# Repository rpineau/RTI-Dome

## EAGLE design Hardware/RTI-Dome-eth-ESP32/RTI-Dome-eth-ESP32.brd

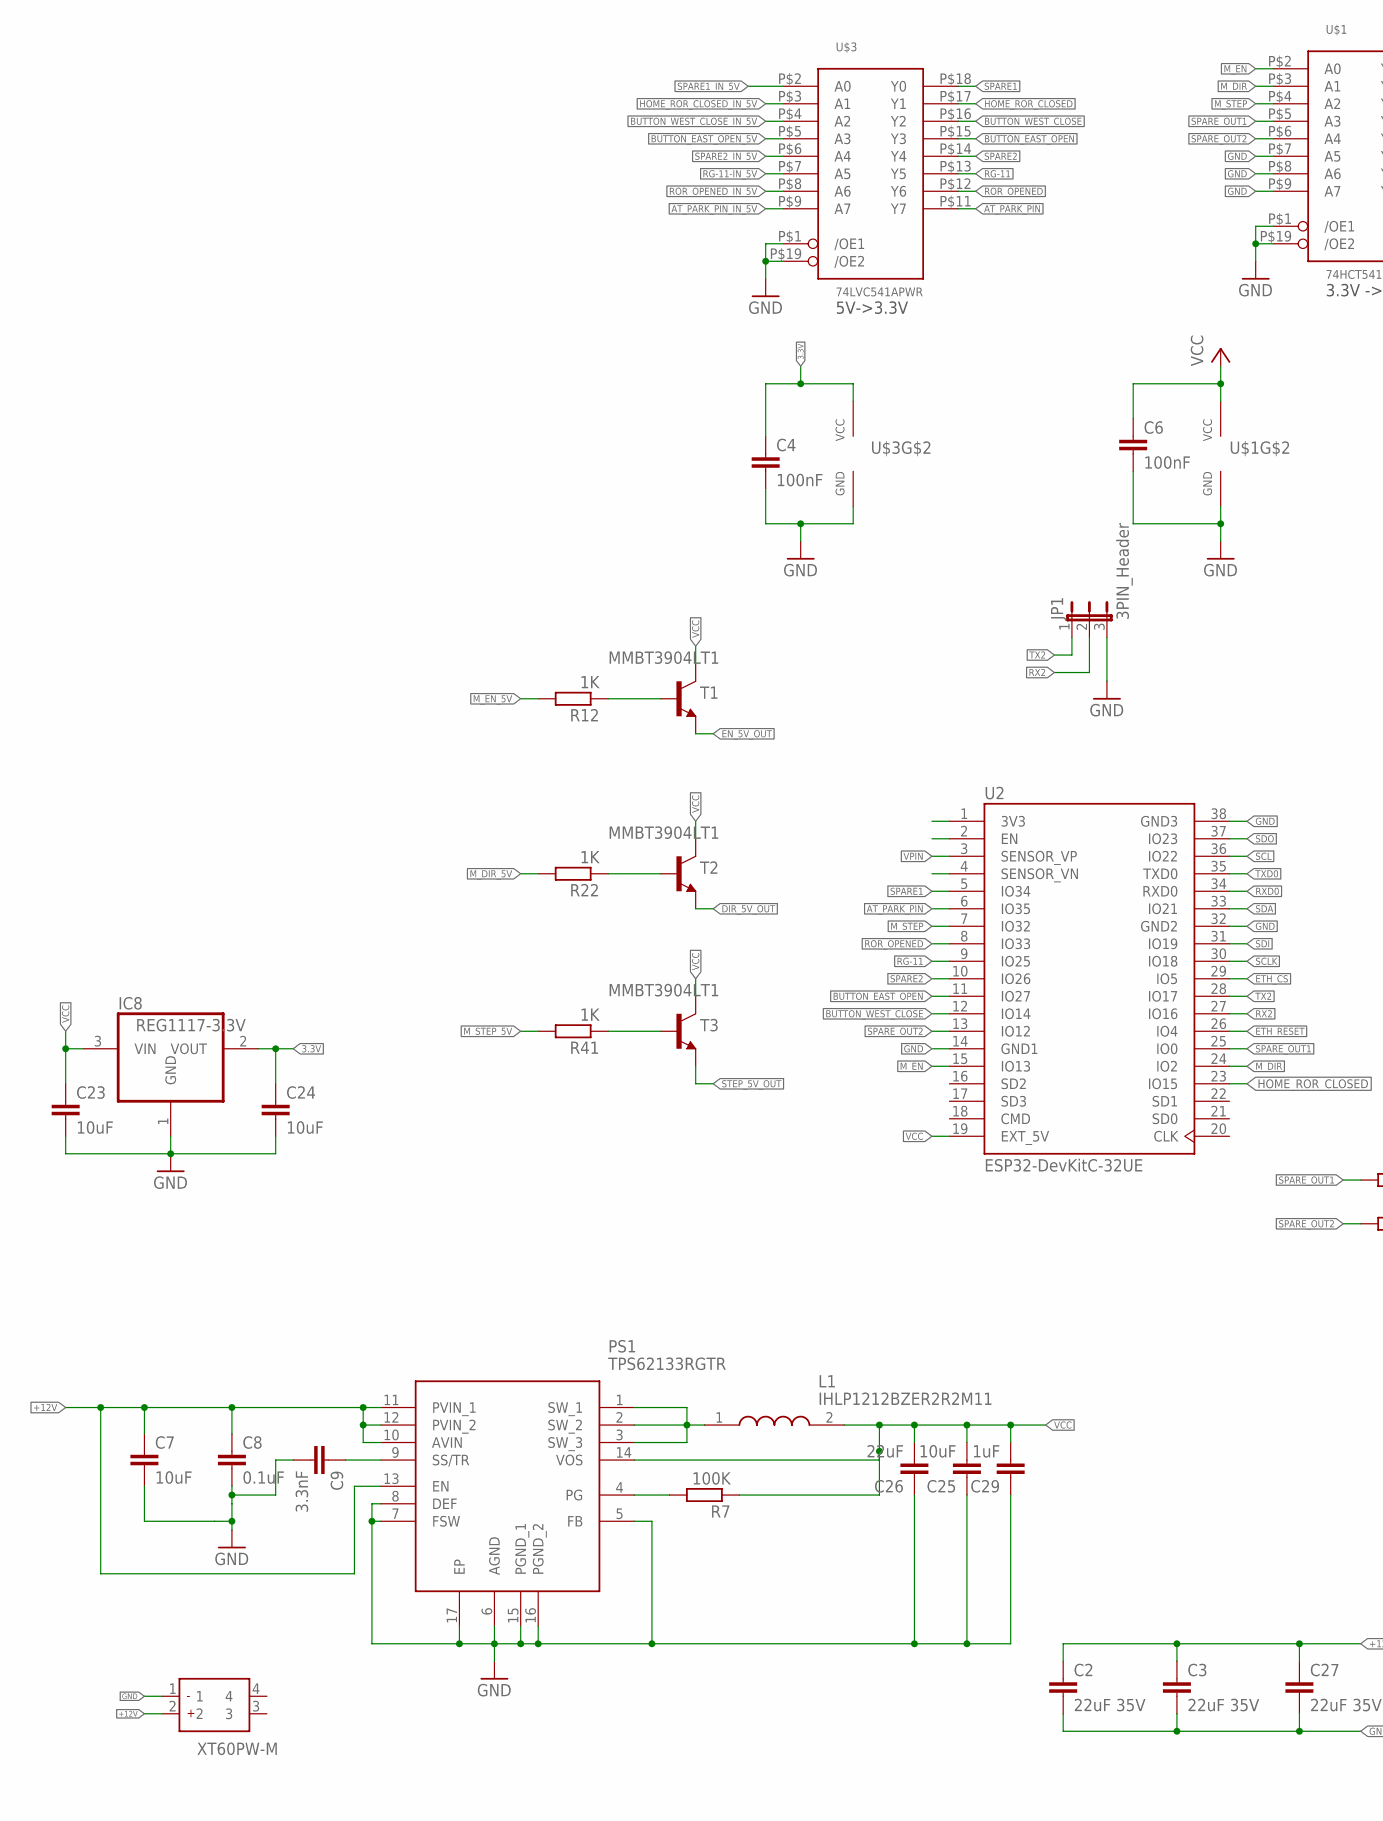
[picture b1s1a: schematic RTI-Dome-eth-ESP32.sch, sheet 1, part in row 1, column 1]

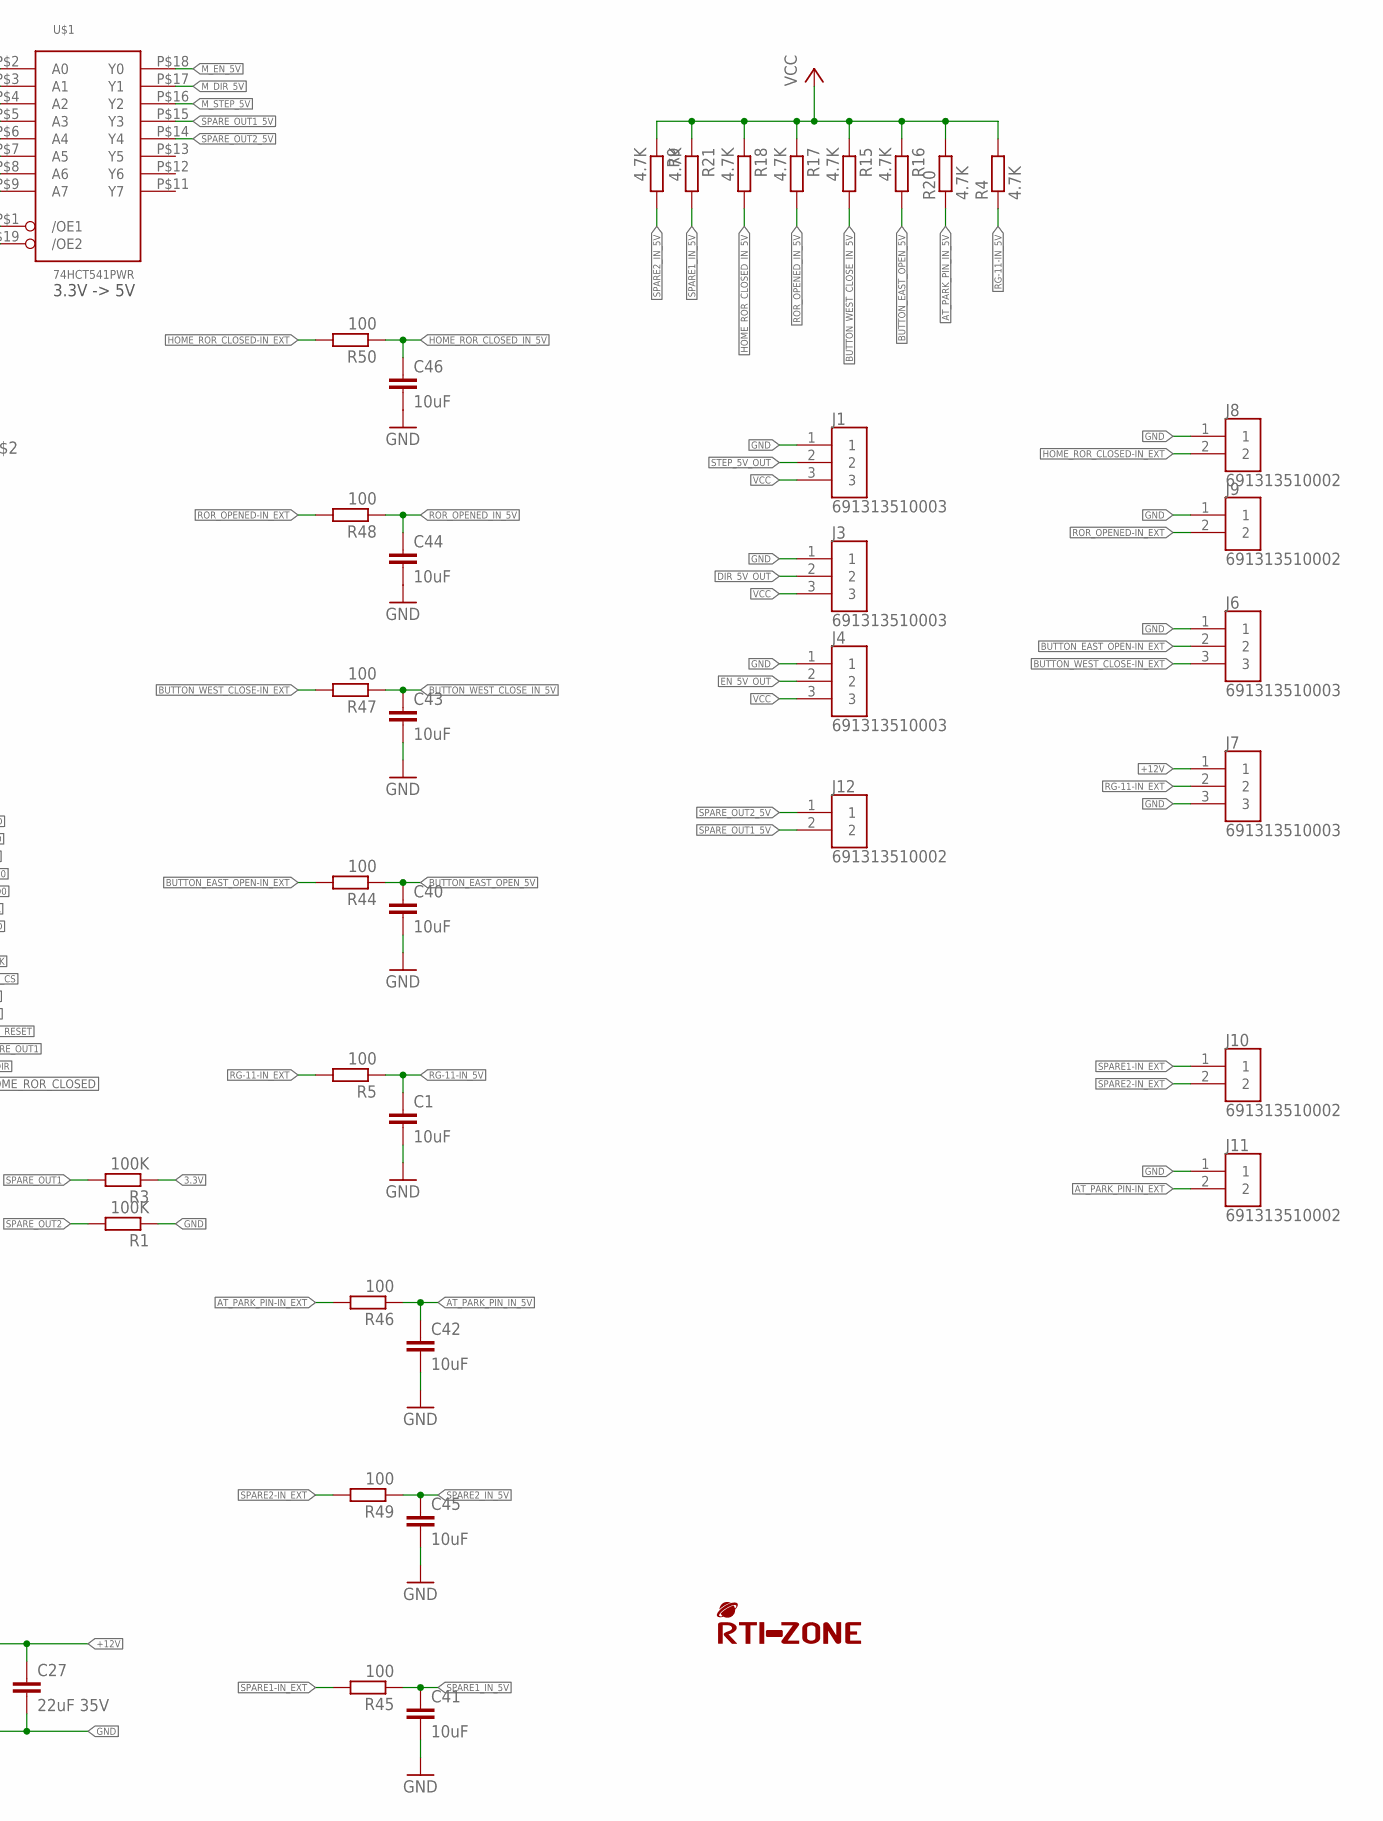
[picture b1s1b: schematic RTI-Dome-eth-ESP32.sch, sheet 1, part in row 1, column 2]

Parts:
C1, C23, C24, C40, C41, C42, C43, C44, C45, C46: 10uF; C0603; MPN CC0805KKX5R8BB106
C2, C3, C27: 22uF 35V; C1206
C4, C6: 100nF; C0603; MPN 0805YD104KAT2A
C7: 10uF; C1206
C8: 0.1uF; C1206
C9: 3.3nF; C0805
C25: 10uF; C0805
C26: 22uF; C0805
C29: 1uF; C0805
IC8: REG1117-3.3V; SOT223; MPN REG1117-3.3/2K5
J1, J3, J4, J6, J7: 691313510003
J2: XT60PW-M; XT60PWM
J8, J9, J10, J11, J12: 691313510002; SHDRRA2W100P0X508_1X2_1216X120
JP1: 3PIN_Header; JP2; LCSC_PART C19190477
L1: IHLP1212BZER2R2M11; INDPM3630X200N
PS1: TPS62133RGTR; QFN50P300X300X100-17N
R1, R3: 100K; R0603; MPN RT0805FRD07100RL
R4, R9, R15, R16, R17, R18, R20, R21: 4.7K; R0603; MPN RT0805FRE074K7L
R5, R44, R45, R46, R47, R48, R49, R50: 100; R0603; MPN RT0805FRD07100RL
R7: 100K; R0603
R12, R22, R41: 1K; R0603; MPN RT0805FRE074K7L
T1, T2, T3: MMBT3904LT1; SOT23
U2: ESP32-DevKitC-32UE; MODULE_ESP32-DEVKITC-32U
U$1: 74HCT541PWR; TSSOP20; LCSC_PART C131314
U$3: 74LVC541APWR; TSSOP20; LCSC_PART C6093
U$4: RTI-LOGO_BIG; LOGO_BIG

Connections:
3.3V: C4.1, C24.1, IC8.2 (VOUT), R3.1, U$3.P$20 (VCC); also elsewhere on the board
+12V: C2.1, C3.1, C7.1, C8.1, C27.1, J2.2, J7.1, PS1.10 (AVIN), PS1.11 (PVIN_1), PS1.12 (PVIN_2), PS1.13 (EN)
AT_PARK_PIN: U2.6 (IO35), U$3.P$11 (Y7)
AT_PARK_PIN-IN_EXT: J11.2, R46.2
AT_PARK_PIN_IN_5V: C42.1, R20.1, R46.1, U$3.P$9 (A7)
BUTTON_EAST_OPEN: U2.11 (IO27), U$3.P$15 (Y3)
BUTTON_EAST_OPEN-IN_EXT: J6.2, R44.2
BUTTON_EAST_OPEN_5V: C40.1, R16.2, R44.1, U$3.P$5 (A3)
BUTTON_WEST_CLOSE: U2.12 (IO14), U$3.P$16 (Y2)
BUTTON_WEST_CLOSE-IN_EXT: J6.3, R47.2
BUTTON_WEST_CLOSE_IN_5V: C43.1, R15.2, R47.1, U$3.P$4 (A2)
DIR-5V_TR: R22.1, T2.1 (B)
DIR_5V_OUT: J3.2, T2.2 (E)
EN-5V_TR: R12.1, T1.1 (B)
EN_5V_OUT: J4.2, T1.2 (E)
ETH_CS: U2.29 (IO5); also elsewhere on the board
ETH_RESET: U2.26 (IO4); also elsewhere on the board
GND: C1.2, C2.2, C3.2, C4.2, C6.2, C7.2, C8.2, C9.2, C23.2, C24.2, C25.1, C26.1, C27.2, C29.1, C40.2, C41.2, C42.2, C43.2, C44.2, C45.2, C46.2, IC8.1 (GND), J1.1, J2.1, J3.1, J4.1, J6.1, J7.3, J8.1, J9.1, J11.1, JP1.3, PS1.5 (FB), PS1.6 (AGND), PS1.7 (FSW), PS1.8 (DEF), PS1.15 (PGND_1), PS1.16 (PGND_2), PS1.17 (EP), R1.1, U2.14 (GND1), U2.32 (GND2), U2.38 (GND3), U$1.P$1 (/OE1), U$1.P$7 (A5), U$1.P$8 (A6), U$1.P$9 (A7), U$1.P$10 (GND), U$1.P$19 (/OE2), U$3.P$1 (/OE1), U$3.P$10 (GND), U$3.P$19 (/OE2); also elsewhere on the board
HOME_ROR_CLOSED: U2.23 (IO15), U$3.P$17 (Y1)
HOME_ROR_CLOSED-IN_EXT: J8.2, R50.2
HOME_ROR_CLOSED_IN_5V: C46.1, R18.2, R50.1, U$3.P$3 (A1)
M_DIR: U2.24 (IO2), U$1.P$3 (A1)
M_DIR_5V: R22.2, U$1.P$17 (Y1)
M_EN: U2.15 (IO13), U$1.P$2 (A0)
M_EN_5V: R12.2, U$1.P$18 (Y0)
M_STEP: U2.7 (IO32), U$1.P$4 (A2)
M_STEP_5V: R41.2, U$1.P$16 (Y2)
PG: PS1.4 (PG), R7.2
RG-11: U2.9 (IO25), U$3.P$13 (Y5)
RG-11-IN_5V: C1.1, R4.1, R5.1, U$3.P$7 (A5)
RG-11-IN_EXT: J7.2, R5.2
ROR_OPENED: U2.8 (IO33), U$3.P$12 (Y6)
ROR_OPENED-IN_EXT: J9.2, R48.2
ROR_OPENED_IN_5V: C44.1, R17.2, R48.1, U$3.P$8 (A6)
RX2: JP1.2, U2.27 (IO16)
RXD0: U2.34 (RXD0)
SCL: U2.36 (IO22)
SCLK: U2.30 (IO18); also elsewhere on the board
SDA: U2.33 (IO21)
SDI: U2.31 (IO19); also elsewhere on the board
SDO: U2.37 (IO23); also elsewhere on the board
SPARE1: U2.5 (IO34), U$3.P$18 (Y0)
SPARE1-IN_EXT: J10.1, R45.2
SPARE1_IN_5V: C41.1, R21.2, R45.1, U$3.P$2 (A0)
SPARE2: U2.10 (IO26), U$3.P$14 (Y4)
SPARE2-IN_EXT: J10.2, R49.2
SPARE2_IN_5V: C45.1, R9.2, R49.1, U$3.P$6 (A4)
SPARE_OUT1: R3.2, U2.25 (IO0), U$1.P$5 (A3)
SPARE_OUT1_5V: J12.2, U$1.P$15 (Y3)
SPARE_OUT2: R1.2, U2.13 (IO12), U$1.P$6 (A4)
SPARE_OUT2_5V: J12.1, U$1.P$14 (Y4)
SS/TR: C9.1, PS1.9 (SS/TR)
STEP-5V_TR: R41.1, T3.1 (B)
STEP_5V_OUT: J1.2, T3.2 (E)
SW: L1.1, PS1.1 (SW_1), PS1.2 (SW_2), PS1.3 (SW_3)
TX2: JP1.1, U2.28 (IO17)
TXD0: U2.35 (TXD0)
VCC: C6.1, C23.1, C25.2, C26.2, C29.2, IC8.3 (VIN), J1.3, J3.3, J4.3, L1.2, PS1.14 (VOS), R4.2, R7.1, R9.1, R15.1, R16.1, R17.1, R18.1, R20.2, R21.1, T1.3 (C), T2.3 (C), T3.3 (C), U2.19 (EXT_5V), U$1.P$20 (VCC)
VPIN: U2.3 (SENSOR_VP)

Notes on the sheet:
5V->3.3V
3.3V -> 5V

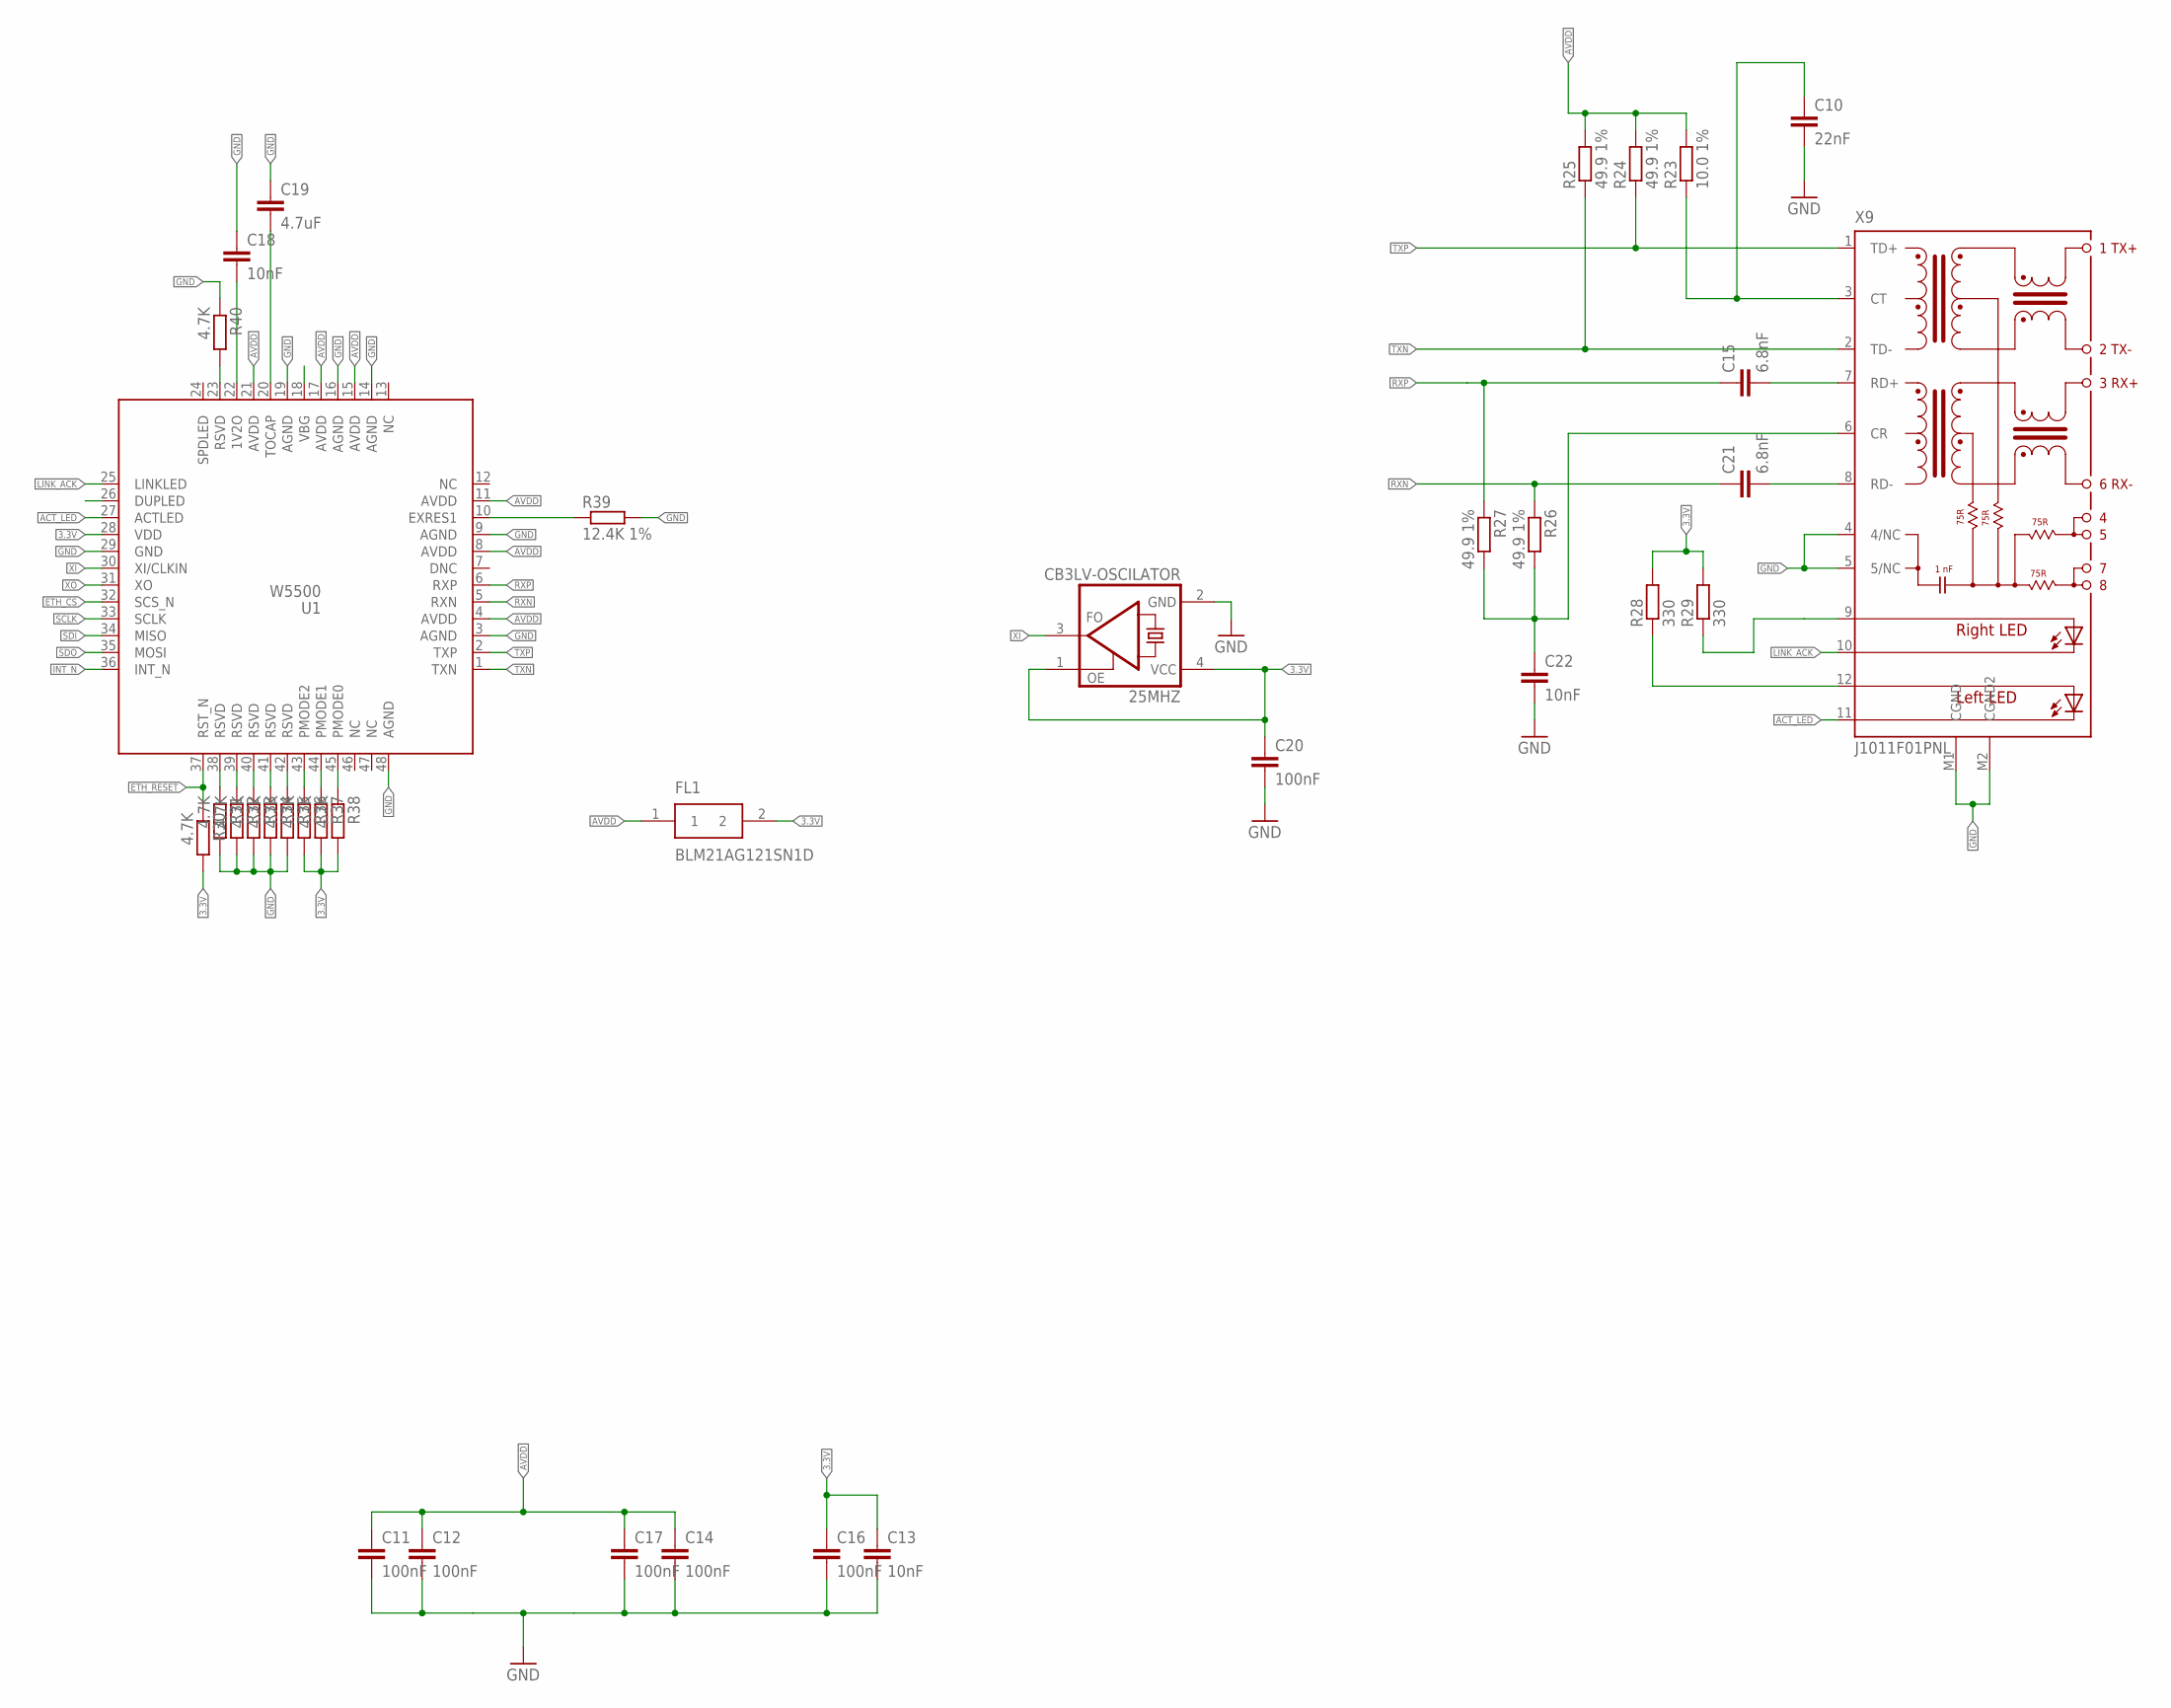
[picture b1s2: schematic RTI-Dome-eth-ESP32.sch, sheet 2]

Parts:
25MHZ: CB3LV-OSCILATOR; SMD-7050_4P; MPN CB3LV-3I-25M0000
C10: 22nF; C0603; MPN CC0805JRX7R8BB223
C11, C12, C14, C16, C17, C20: 100nF; C0603; MPN 0805YD104KAT2A
C13, C18, C22: 10nF; C0603; MPN CC0805KRX7R9BB103
C15, C21: 6.8nF; C0603; MPN C0805C682F4HACTU
C19: 4.7uF; C0603; MPN C0805C475J3RACTU
FL1: BLM21AG121SN1D; L0805; MPN BLM21AG121SN1D
R23: 10.0 1%; R0603; MPN C881123
R24, R25, R26, R27: 49.9 1%; R0603; MPN RC0805FR-0749R9L
R28, R29: 330; R0603; MPN RC0805JR-07330RL
R30, R31, R32, R33, R34, R35, R36, R37, R38, R40: 4.7K; R0603; MPN RT0805FRE074K7L
R39: 12.4K 1%; R0603; MPN RC0805FR-0712K4L
U1: W5500; LQFP48; MPN W5500
X9: J1011F01PNL

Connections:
3.3V: 25MHZ.1 (OE), 25MHZ.4 (VDD), C13.1, C16.1, C20.1, FL1.2, R28.2, R29.2, R30.2, R36.2, R37.2, R38.2, U1.28 (VDD); also elsewhere on the board
ACT_LED: U1.27 (ACTLED), X9.11 (C-L)
AVDD: C11.1, C12.1, C14.1, C17.1, FL1.1, R23.2, R24.2, R25.2, U1.4 (AVDD), U1.8 (AVDD), U1.11 (AVDD), U1.15 (AVDD), U1.17 (AVDD), U1.21 (AVDD)
CR: C22.1, R26.2, R27.2, X9.6 (CR)
CT: C10.1, R23.1, X9.3 (CT)
ETH_CS: U1.32 (SCS_N); also elsewhere on the board
ETH_RESET: R30.1, U1.37 (RST_N); also elsewhere on the board
GND: 25MHZ.2 (GND), C10.2, C11.2, C12.2, C13.2, C14.2, C16.2, C17.2, C18.1, C19.1, C20.2, C22.2, R31.2, R32.2, R33.2, R34.2, R35.2, R39.2, R40.1, U1.3 (AGND), U1.9 (AGND), U1.14 (AGND), U1.16 (AGND), U1.19 (AGND), U1.29 (GND), U1.48 (AGND), X9.4 (4/NC), X9.5 (5/NC), X9.M1 (CGND), X9.M2 (CGND2); also elsewhere on the board
INT_N: U1.36 (INT_N)
LINK_ACK: U1.25 (LINKLED), X9.10 (C-R)
L_LED+: R28.1, X9.12 (AL)
unnamed: R31.1, U1.38 (RSVD)
unnamed: R32.1, U1.39 (RSVD)
unnamed: R33.1, U1.40 (RSVD)
unnamed: R34.1, U1.41 (RSVD)
unnamed: R35.1, U1.42 (RSVD)
unnamed: R36.1, U1.43 (PMODE2)
unnamed: R37.1, U1.44 (PMODE1)
unnamed: R38.1, U1.45 (PMODE0)
unnamed: C19.2, U1.20 (TOCAP)
unnamed: C18.2, U1.22 (1V2O)
unnamed: R39.1, U1.10 (EXRES1)
unnamed: R40.2, U1.23 (RSVD)
RD+: C15.2, X9.7 (RD+)
RD-: C21.2, X9.8 (RD-)
RXN: C21.1, R26.1, U1.5 (RXN)
RXP: C15.1, R27.1, U1.6 (RXP)
R_LED+: R29.1, X9.9 (A-R)
SCLK: U1.33 (SCLK); also elsewhere on the board
SDI: U1.34 (MISO); also elsewhere on the board
SDO: U1.35 (MOSI); also elsewhere on the board
TXN: R25.1, U1.1 (TXN), X9.2 (TD-)
TXP: R24.1, U1.2 (TXP), X9.1 (TD+)
XI: 25MHZ.3 (FO), U1.30 (XI/CLKIN)
XO: U1.31 (XO)

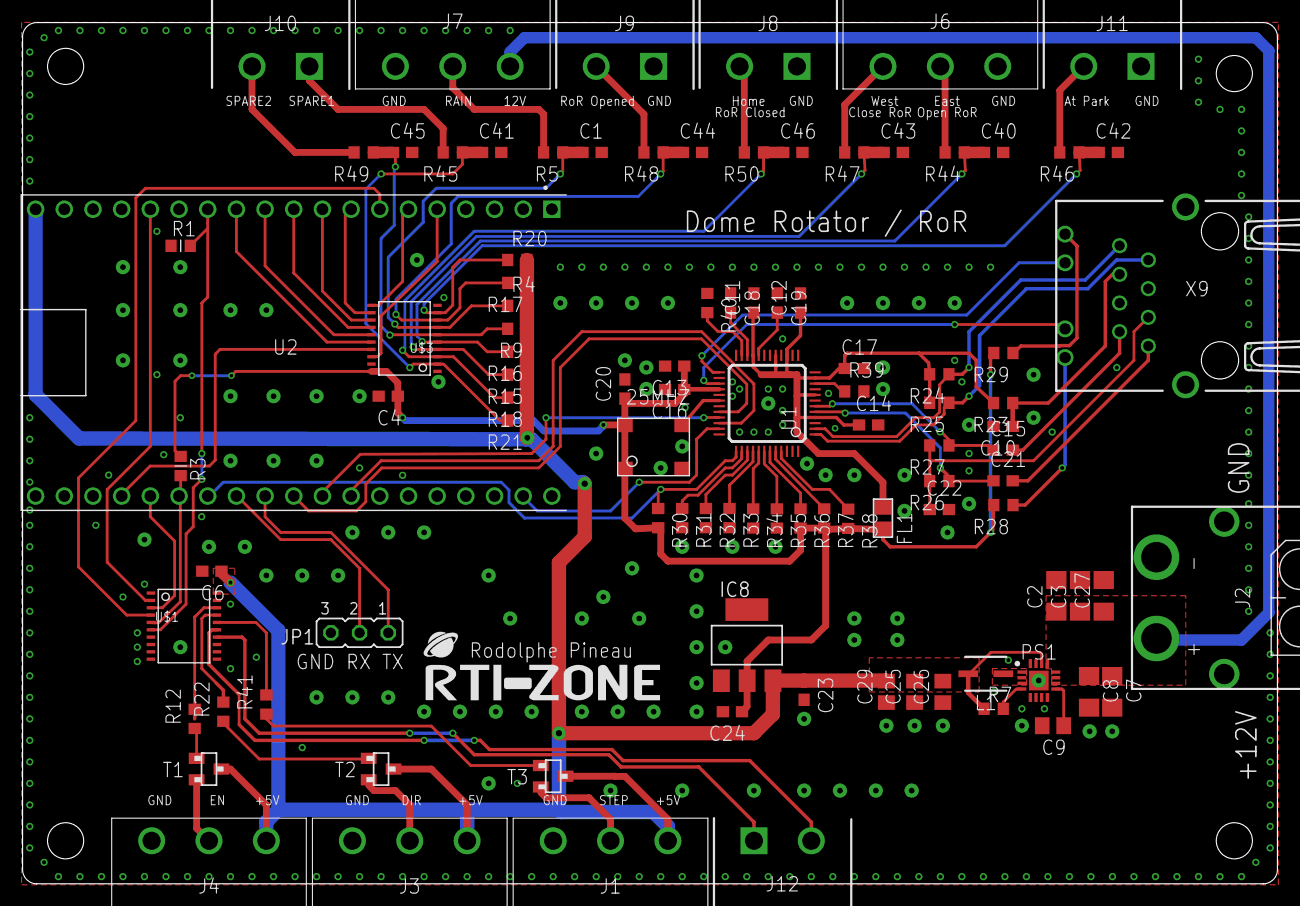
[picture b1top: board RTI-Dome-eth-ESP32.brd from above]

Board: 2 copper layers, 111.1 x 76.3 mm, 100 parts (0 on the bottom side), 80 nets.

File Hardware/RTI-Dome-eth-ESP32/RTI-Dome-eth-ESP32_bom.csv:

Comment,Designator,Footprint,LCSC Part #
0.1uF,C8,C1206,
1K,R12 R22 R41,R0603,
1uF,C29,C0805,
3.3nF,C9,C0805,
3PIN_Header,JP1,JP2,C19190477
4.7K,R4 R9 R15 R16 R17 R18 R20 R21 R30 R31 R32 R33 R34 R35 R36 R37 R38 R40,R0603,
4.7uF,C19,C0603,
6.8nF,C15 C21,C0603,
10.0 1%,R23,R0603,
10nF,C13 C18 C22,C0603,
10uF,C1,C0603,
10uF,C7,C1206,
10uF,C23 C24,C0603,
10uF,C25,C0805,
10uF,C40 C41 C42 C43 C44 C45 C46,C0603,
12.4K 1%,R39,R0603,
22nF,C10,C0603,
22uF,C26,C0805,
22uF 35V,C2 C3 C27,C1206,
49.9 1%,R24 R25 R26 R27,R0603,
74HCT541PWR,U$1,TSSOP20,C131314
74LVC541APWR,U$3,TSSOP20,C6093
100,R5 R44 R45 R46 R47 R48 R49 R50,R0603,
100K,R1 R3 R7,R0603,
100nF,C4 C6 C11 C12 C14 C16 C17 C20,C0603,
330,R28 R29,R0603,
691313510002,J8 J9 J10 J11 J12,SHDRRA2W100P0X508_1X2_1216X120,
691313510003,J1 J3 J4 J6 J7,691313510003,
BLM21AG121SN1D,FL1,L0805,
CB3LV-OSCILATOR,25MHZ,SMD-7050_4P,
ESP32-DevKitC-32UE,U2,MODULE_ESP32-DEVKITC-32U,
IHLP1212BZER2R2M11,L1,INDPM3630X200N,C553996
J1011F01PNL,X9,J1011F01PNL,
MMBT3904LT1,T1 T2 T3,SOT23,
REG1117-3.3V,IC8,SOT223,
RTI-LOGO_BIG,U$4,LOGO_BIG,
TPS62133RGTR,PS1,QFN50P300X300X100-17N,C73973
W5500,U1,LQFP48,
XT60PW-M,J2,XT60PWM,C98732

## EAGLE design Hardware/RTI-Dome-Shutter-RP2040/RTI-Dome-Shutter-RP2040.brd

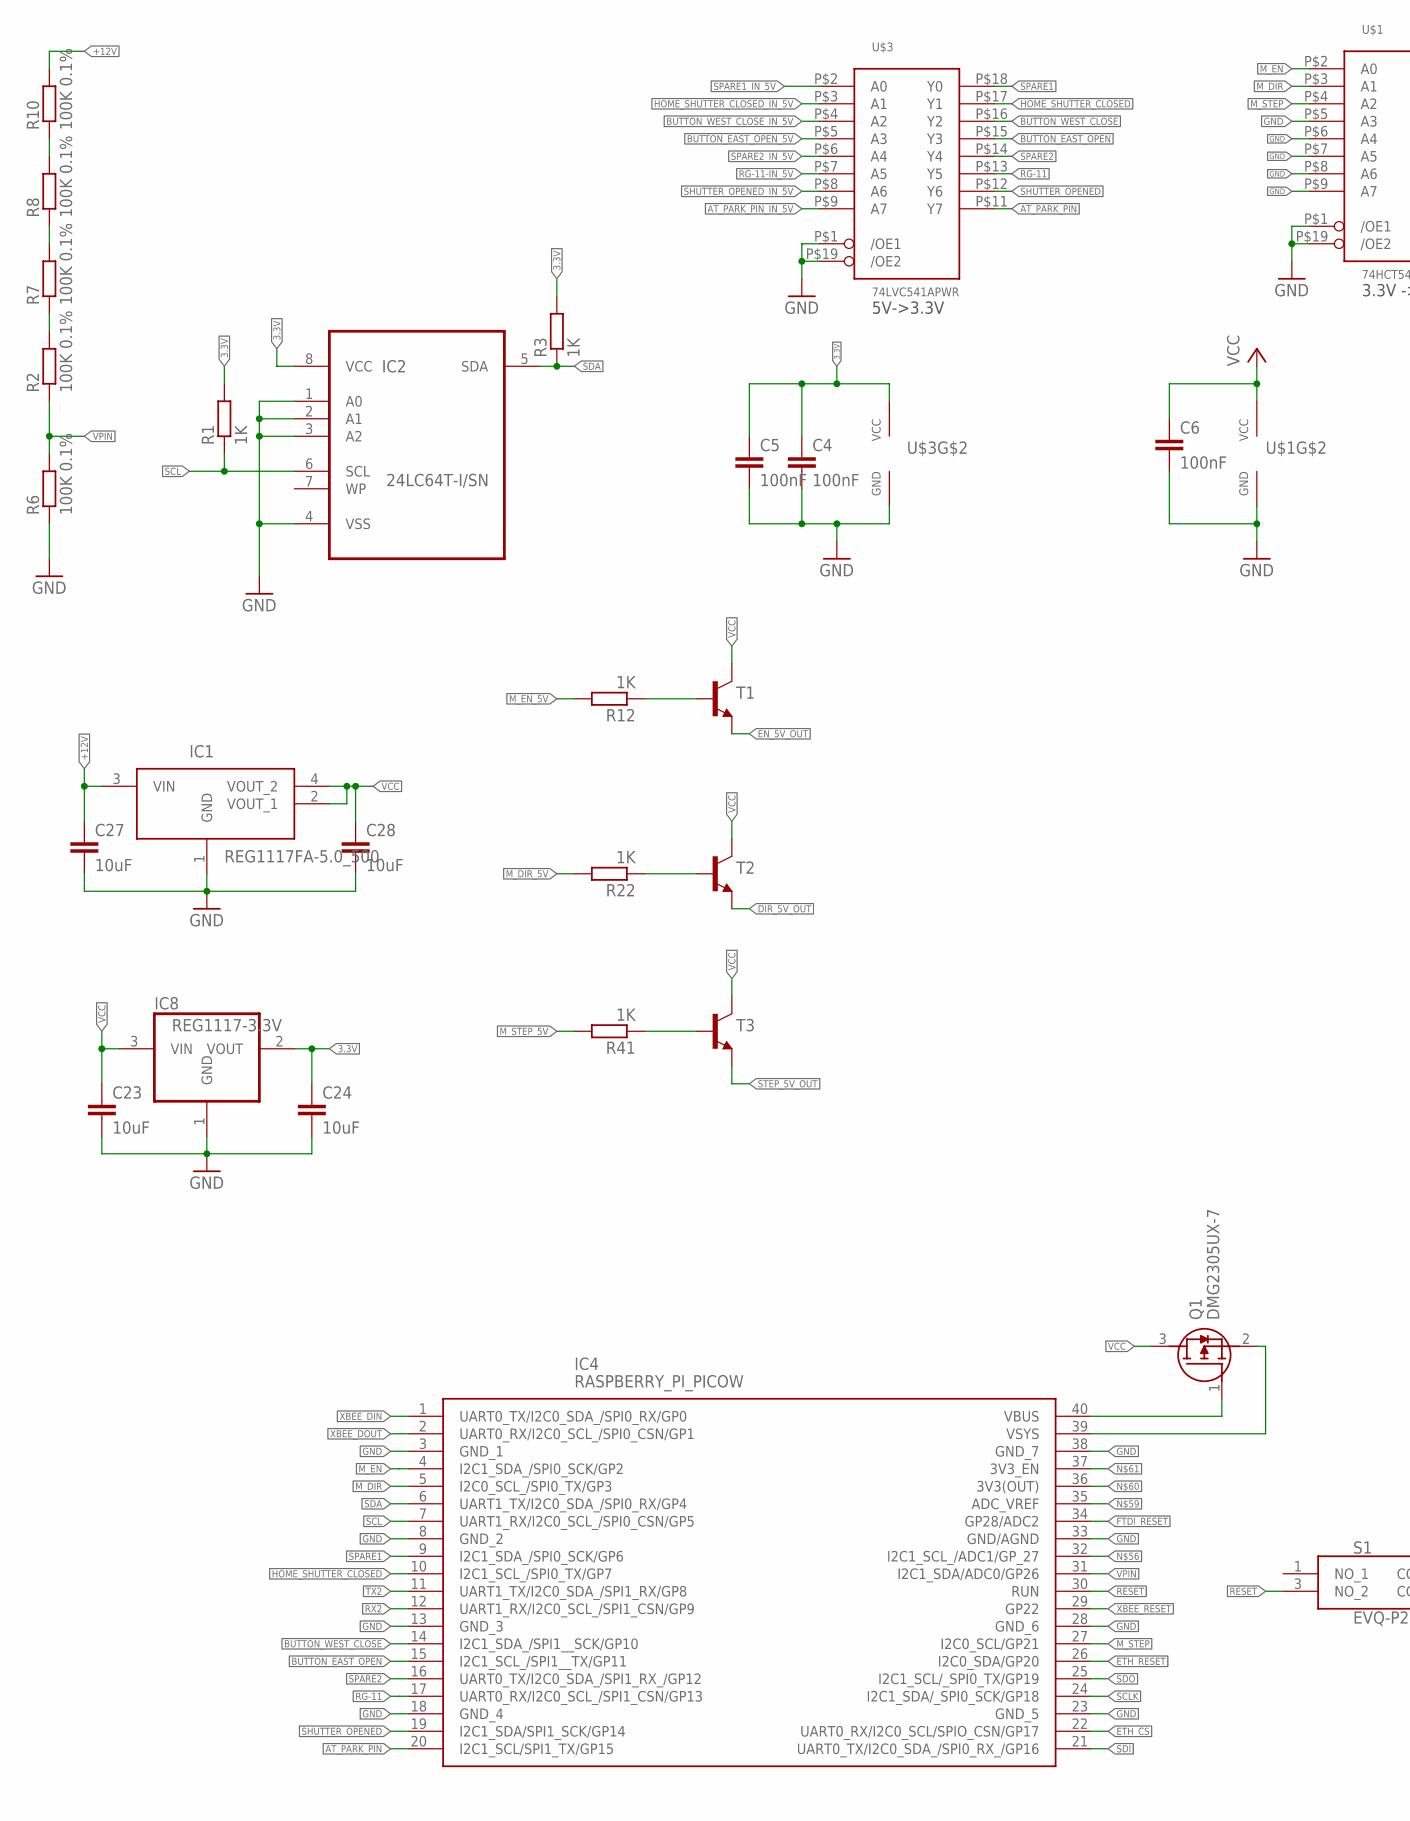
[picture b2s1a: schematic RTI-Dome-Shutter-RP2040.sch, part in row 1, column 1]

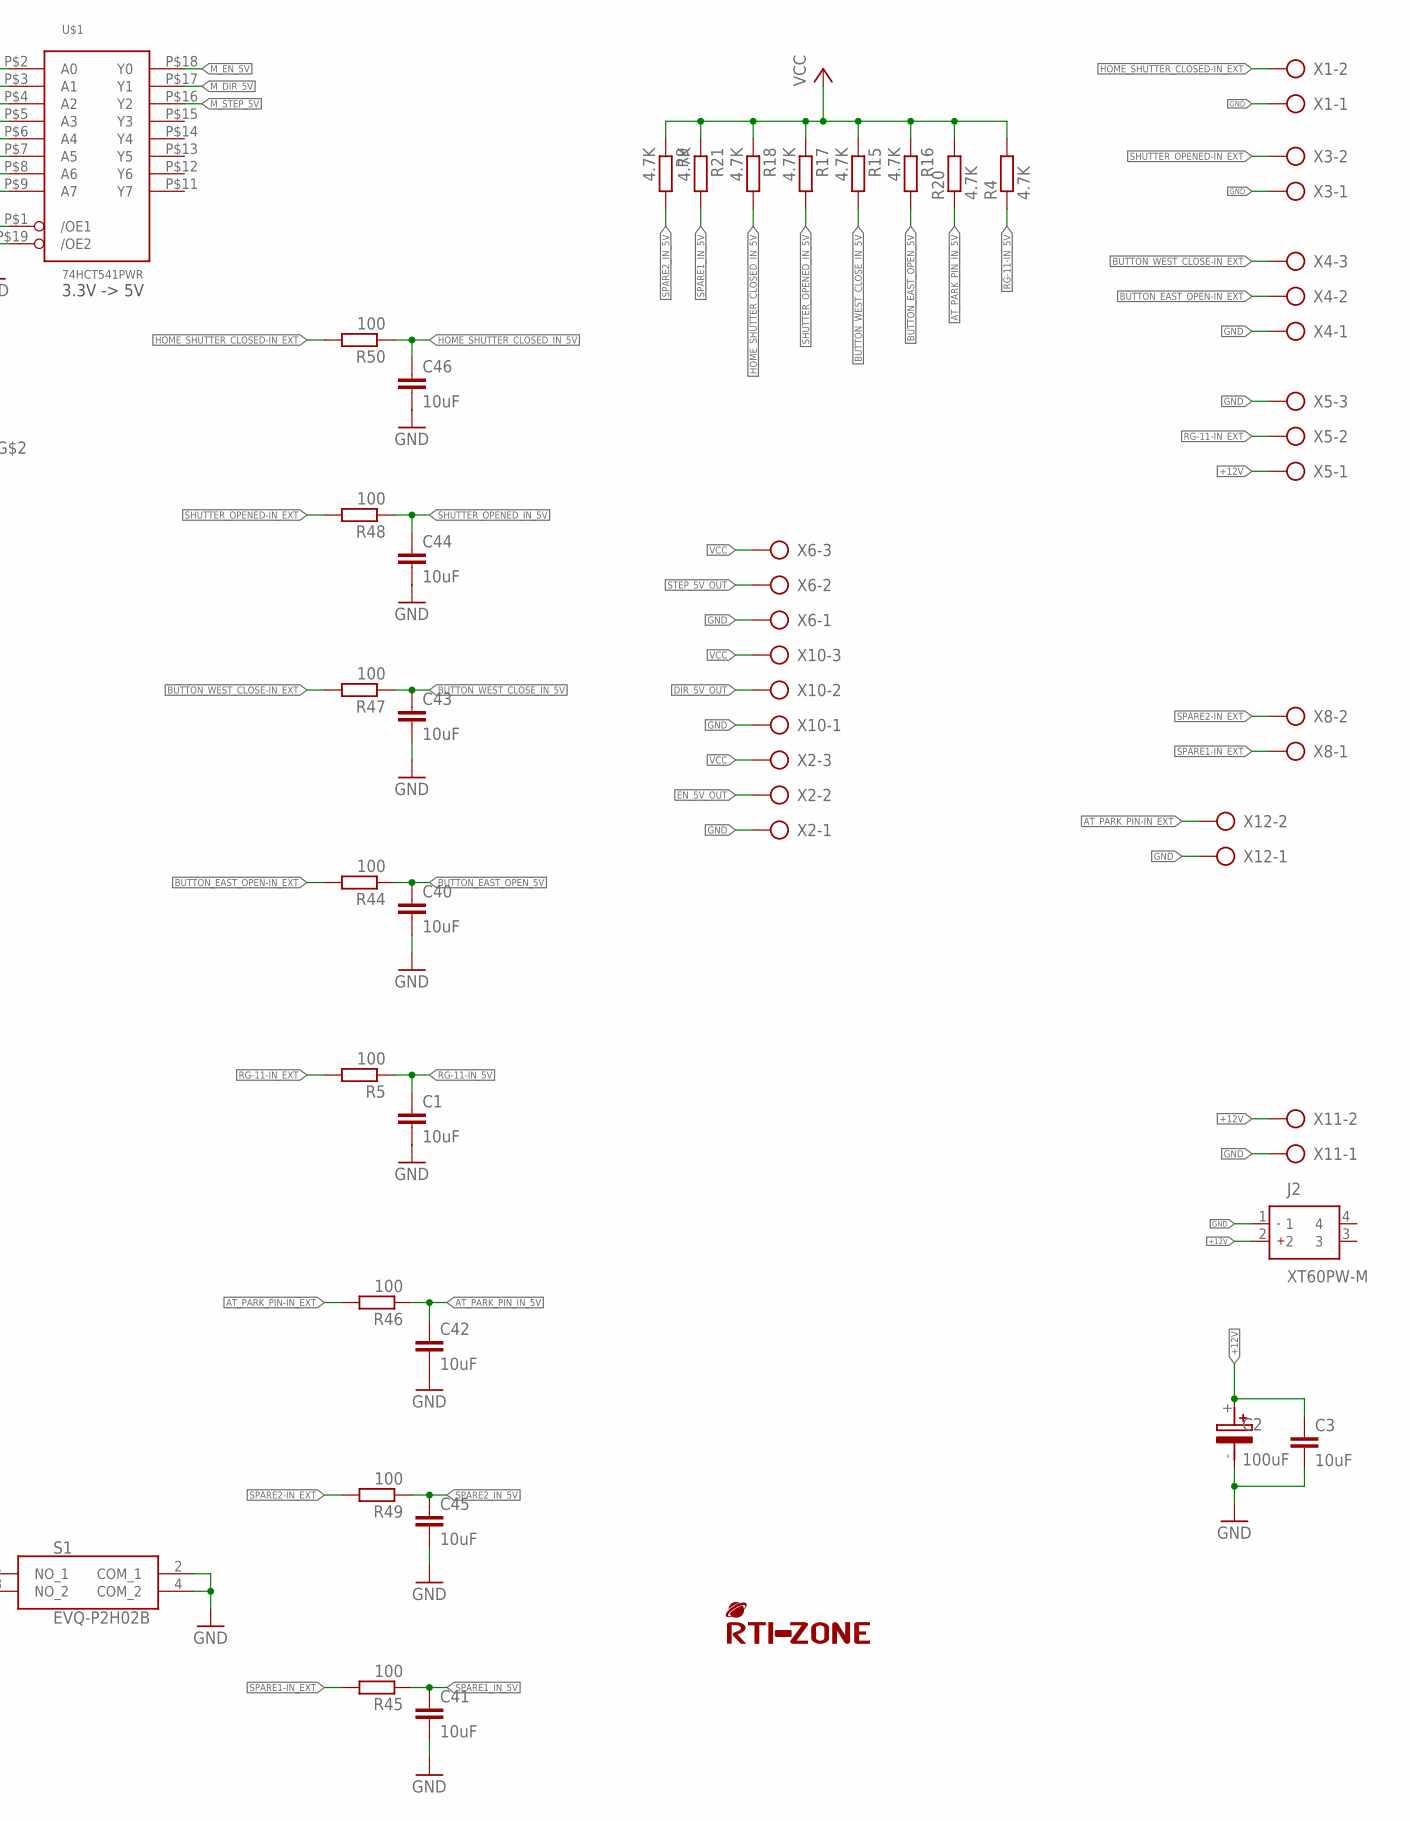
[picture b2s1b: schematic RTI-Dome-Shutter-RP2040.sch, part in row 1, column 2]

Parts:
C1, C3, C23, C24, C27, C28, C40, C41, C42, C43, C44, C45, C46: 10uF; C0603; MPN CC0805KKX5R8BB106
C2: 100uF; UD-10X10_NICHICON; MPN MAL215099804E3
C4, C5, C6: 100nF; C0603; MPN 0805YD104KAT2A
IC1: REG1117FA-5.0_500; REG1117FA50500
IC2: 24LC64T-I/SN; SOIC127P600X175-8N
IC4: RASPBERRY_PI_PICOW; RASPBERRYPIPICO-W
IC8: REG1117-3.3V; SOT223; MPN REG1117-3.3/2K5
J2: XT60PW-M; XT60PWM
Q1: DMG2305UX-7; SOT96P240X115-3N
R1, R3: 1K; R0603; MPN RT0805FRE071KL
R2, R6, R7, R8, R10: 100K 0.1%; R0603; MPN AT0805BRD07100KL
R4, R9, R15, R16, R17, R18, R20, R21: 4.7K; R0603; MPN RT0805FRE074K7L
R5, R44, R45, R46, R47, R48, R49, R50: 100; R0603; MPN RT0805FRD07100RL
R12, R22, R41: 1K; R0603; MPN RT0805FRE074K7L
S1: EVQ-P2H02B; EVQP2H02B
T1, T2, T3: MMBT3904LT1-NPN-SOT23-BEC; SOT23-BEC
U$1: 74HCT541PWR; TSSOP20
U$3: 74LVC541APWR; TSSOP20
U$4: RTI-LOGO_BIG; LOGO_BIG
X1, X3, X8, X11, X12: AK500/2; MPN 691101710002
X2, X6, X10: AK500/3
X4, X5: AK500/3; MPN 691101710003

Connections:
3.3V: C4.1, C5.1, C24.1, IC2.8 (VCC), IC8.2 (VOUT), R1.2, R3.2, U$3.P$20 (VCC)
+12V: C2.+, C3.1, C27.1, IC1.3 (VIN), J2.2, R10.2, X5.1, X11.2
AT_PARK_PIN: IC4.20 (I2C1_SCL/SPI1_TX/GP15), U$3.P$11 (Y7)
AT_PARK_PIN-IN_EXT: R46.2, X12.2
AT_PARK_PIN_IN_5V: C42.1, R20.1, R46.1, U$3.P$9 (A7)
BUTTON_EAST_OPEN: IC4.15 (I2C1_SCL_/SPI1__TX/GP11), U$3.P$15 (Y3)
BUTTON_EAST_OPEN-IN_EXT: R44.2, X4.2
BUTTON_EAST_OPEN_5V: C40.1, R16.2, R44.1, U$3.P$5 (A3)
BUTTON_WEST_CLOSE: IC4.14 (I2C1_SDA_/SPI1__SCK/GP10), U$3.P$16 (Y2)
BUTTON_WEST_CLOSE-IN_EXT: R47.2, X4.3
BUTTON_WEST_CLOSE_IN_5V: C43.1, R15.2, R47.1, U$3.P$4 (A2)
DIR-5V_TR: R22.1, T2.B
DIR_5V_OUT: T2.E, X10.2
EN-5V_TR: R12.1, T1.B
EN_5V_OUT: T1.E, X2.2
ETH_CS: IC4.22 (UART0_RX/I2C0_SCL/SPIO_CSN/GP17)
ETH_RESET: IC4.26 (I2C0_SDA/GP20)
FTDI_RESET: IC4.34 (GP28/ADC2)
GND: C1.2, C2.-, C3.2, C4.2, C5.2, C6.2, C23.2, C24.2, C27.2, C28.2, C40.2, C41.2, C42.2, C43.2, C44.2, C45.2, C46.2, IC1.1 (GND), IC2.1 (A0), IC2.2 (A1), IC2.3 (A2), IC2.4 (VSS), IC4.3 (GND_1), IC4.8 (GND_2), IC4.13 (GND_3), IC4.18 (GND_4), IC4.23 (GND_5), IC4.28 (GND_6), IC4.33 (GND/AGND), IC4.38 (GND_7), IC8.1 (GND), J2.1, R6.1, S1.2 (COM_1), S1.4 (COM_2), U$1.P$1 (/OE1), U$1.P$5 (A3), U$1.P$6 (A4), U$1.P$7 (A5), U$1.P$8 (A6), U$1.P$9 (A7), U$1.P$10 (GND), U$1.P$19 (/OE2), U$3.P$1 (/OE1), U$3.P$10 (GND), U$3.P$19 (/OE2), X1.1, X2.1, X3.1, X4.1, X5.3, X6.1, X10.1, X11.1, X12.1
HOME_SHUTTER_CLOSED: IC4.10 (I2C1_SCL_/SPI0_TX/GP7), U$3.P$17 (Y1)
HOME_SHUTTER_CLOSED-IN_EXT: R50.2, X1.2
HOME_SHUTTER_CLOSED_IN_5V: C46.1, R18.2, R50.1, U$3.P$3 (A1)
M_DIR: IC4.5 (I2C0_SCL_/SPI0_TX/GP3), U$1.P$3 (A1)
M_DIR_5V: R22.2, U$1.P$17 (Y1)
M_EN: IC4.4 (I2C1_SDA_/SPI0_SCK/GP2), U$1.P$2 (A0)
M_EN_5V: R12.2, U$1.P$18 (Y0)
M_STEP: IC4.27 (I2C0_SCL/GP21), U$1.P$4 (A2)
M_STEP_5V: R41.2, U$1.P$16 (Y2)
unnamed: R7.2, R8.1
unnamed: R8.2, R10.1
unnamed: R2.2, R7.1
RESET: IC4.30 (RUN), S1.3 (NO_2)
RG-11: IC4.17 (UART0_RX/I2C0_SCL_/SPI1_CSN/GP13), U$3.P$13 (Y5)
RG-11-IN_5V: C1.1, R4.1, R5.1, U$3.P$7 (A5)
RG-11-IN_EXT: R5.2, X5.2
RX2: IC4.12 (UART1_RX/I2C0_SCL_/SPI1_CSN/GP9)
SCL: IC2.6 (SCL), IC4.7 (UART1_RX/I2C0_SCL_/SPI0_CSN/GP5), R1.1
SCLK: IC4.24 (I2C1_SDA/_SPI0_SCK/GP18)
SDA: IC2.5 (SDA), IC4.6 (UART1_TX/I2C0_SDA_/SPI0_RX/GP4), R3.1
SDI: IC4.21 (UART0_TX/I2C0_SDA_/SPI0_RX_/GP16)
SDO: IC4.25 (I2C1_SCL/_SPI0_TX/GP19)
SHUTTER_OPENED: IC4.19 (I2C1_SDA/SPI1_SCK/GP14), U$3.P$12 (Y6)
SHUTTER_OPENED-IN_EXT: R48.2, X3.2
SHUTTER_OPENED_IN_5V: C44.1, R17.2, R48.1, U$3.P$8 (A6)
SPARE1: IC4.9 (I2C1_SDA_/SPI0_SCK/GP6), U$3.P$18 (Y0)
SPARE1-IN_EXT: R45.2, X8.1
SPARE1_IN_5V: C41.1, R21.2, R45.1, U$3.P$2 (A0)
SPARE2: IC4.16 (UART0_TX/I2C0_SDA_/SPI1_RX_/GP12), U$3.P$14 (Y4)
SPARE2-IN_EXT: R49.2, X8.2
SPARE2_IN_5V: C45.1, R9.2, R49.1, U$3.P$6 (A4)
STEP-5V_TR: R41.1, T3.B
STEP_5V_OUT: T3.E, X6.2
TX2: IC4.11 (UART1_TX/I2C0_SDA_/SPI1_RX/GP8)
VBUS: IC4.40 (VBUS), Q1.1 (G)
VCC: C6.1, C23.1, C28.1, IC1.2 (VOUT_1), IC1.4 (VOUT_2), IC8.3 (VIN), Q1.3 (D), R4.2, R9.1, R15.1, R16.1, R17.1, R18.1, R20.2, R21.1, T1.C, T2.C, T3.C, U$1.P$20 (VCC), X2.3, X6.3, X10.3
VPIN: IC4.31 (I2C1_SDA/ADC0/GP26), R2.1, R6.2
VSYS: IC4.39 (VSYS), Q1.2 (S)
XBEE_DIN: IC4.1 (UART0_TX/I2C0_SDA_/SPI0_RX/GP0)
XBEE_DOUT: IC4.2 (UART0_RX/I2C0_SCL_/SPI0_CSN/GP1)
XBEE_RESET: IC4.29 (GP22)

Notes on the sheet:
5V->3.3V
3.3V -> 5V
